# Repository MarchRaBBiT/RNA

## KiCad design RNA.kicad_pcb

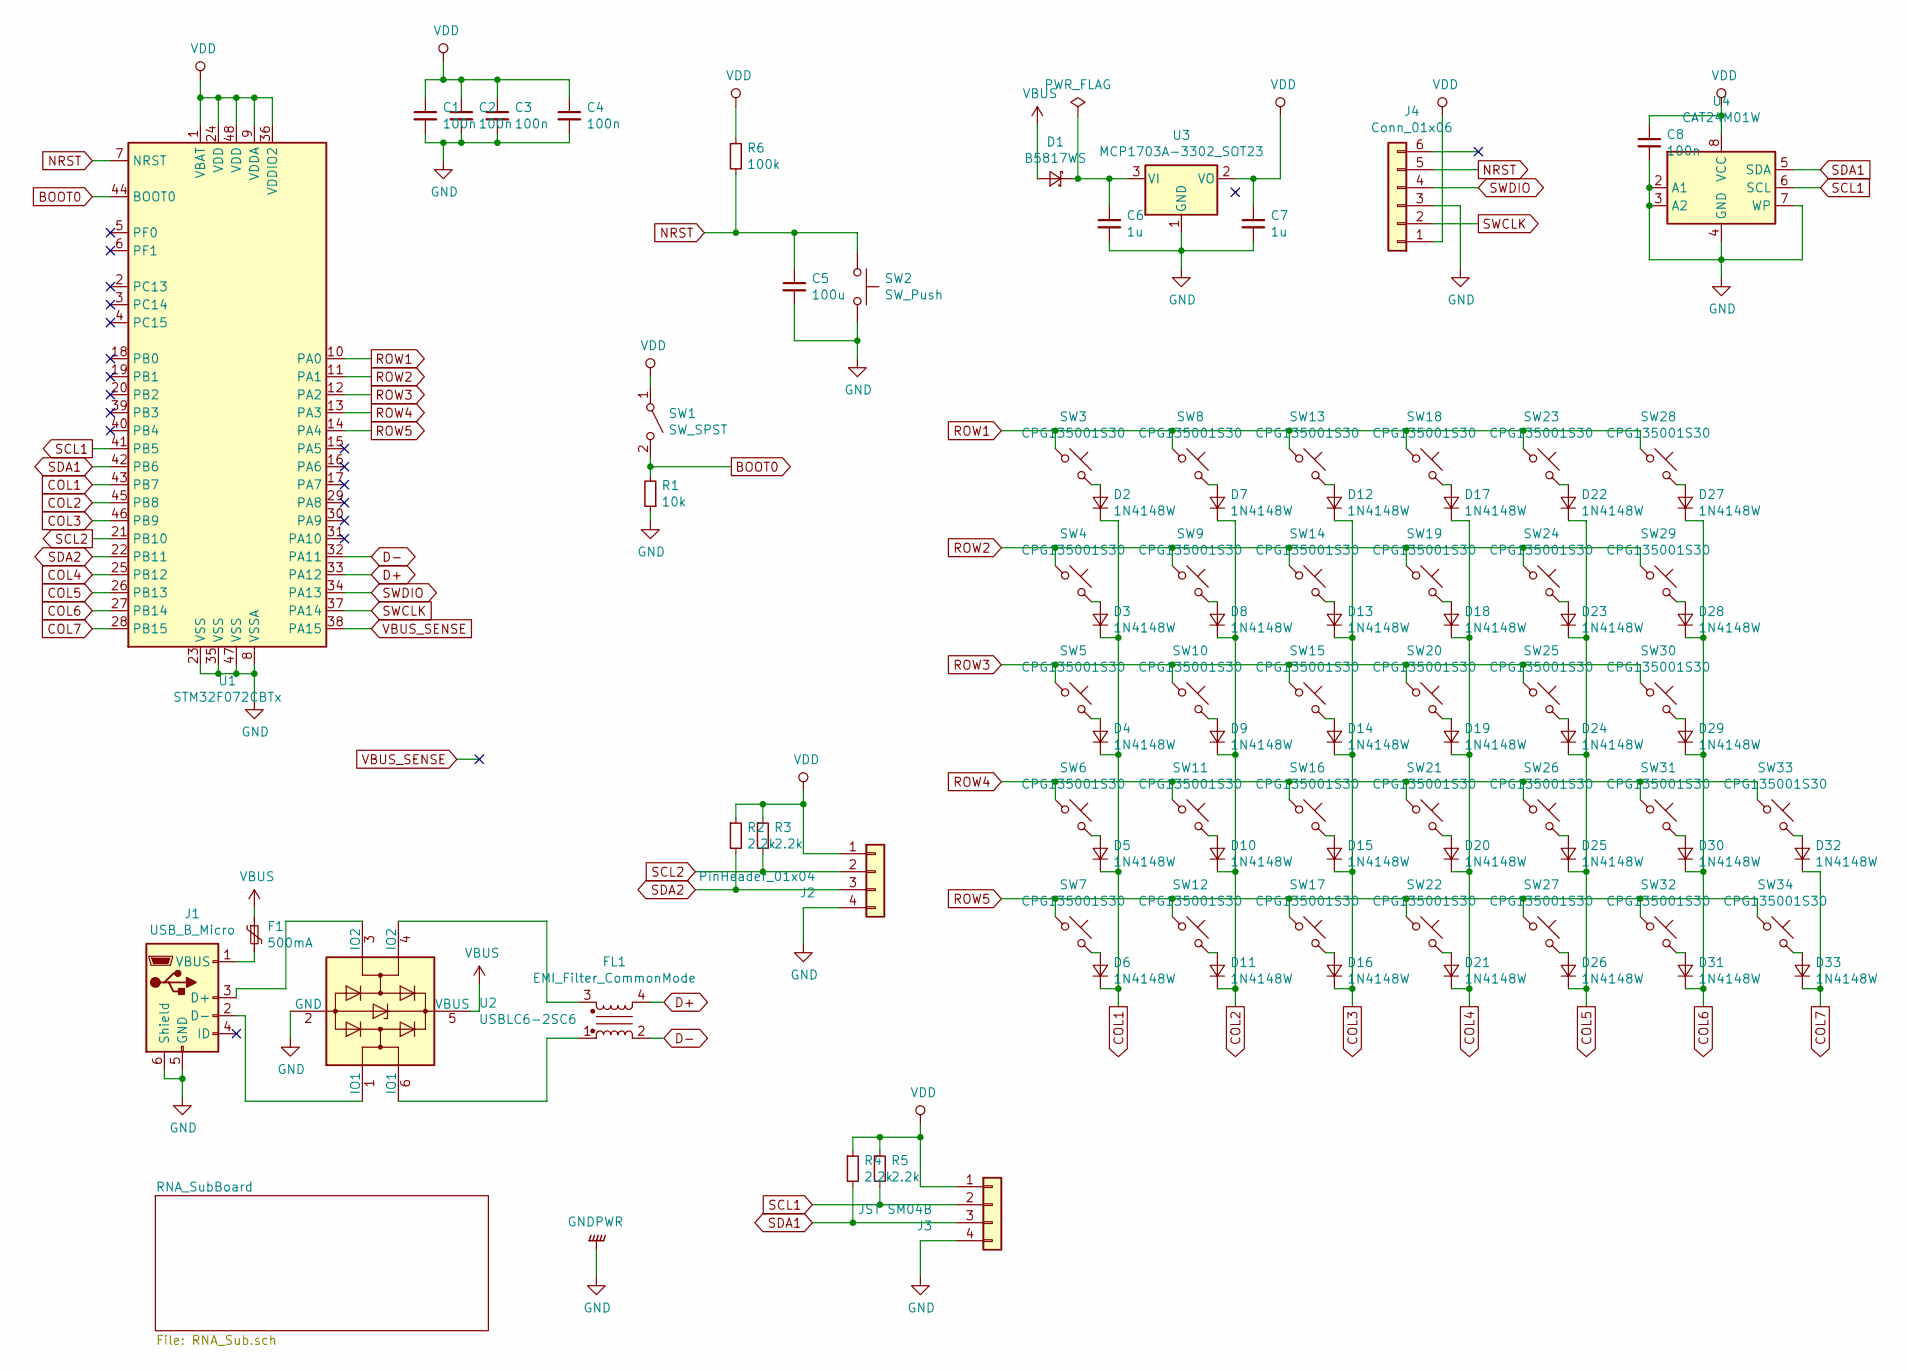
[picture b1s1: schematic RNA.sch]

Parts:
C1, C2, C3, C4, C8: 100n; C_0603_1608Metric; LCSC_Parts_No C14663
C5: 100u; C_0603_1608Metric; LCSC_Parts_No C14663
C6, C7: 1u; C_0603_1608Metric; LCSC_Parts_No C15849
D1: B5817WS; D_SOD-323; LCSC_Parts_No C179720
D2, D3, D4, D5, D6, D7, D8, D9, D10, D11, D12, D13, D14, D15, D16, D17, D18, D19, D20, D21, D22, D23, D24, D25, D26, D27, D28, D29, D30, D31, D32, D33: 1N4148W; D_SOD-123; LCSC_Parts_No C81598
F1: 500mA; Fuse_1206_3216Metric; LCSC_Parts_No C261942
FL1: EMI_Filter_CommonMode; ACM2012-121-2P-T002; LCSC_Parts_No C76571
J1: USB_B_Micro; USB_Micro-B_Molex-105017-0001
J2: PinHeader_01x04; PinHeader_1x04_P2.54mm_Vertical
J3: JST SM04B; JST_SH_SM04B-SRSS-TB_1x04-1MP_P1.00mm_Horizontal
J4: Conn_01x06; PinHeader_2x03_P2.54mm_Vertical
R1: 10k; R_0603_1608Metric; LCSC_Parts_No C25804
R2, R3, R4, R5: 2.2k; R_0603_1608Metric; LCSC_Parts_No C4190
R6: 100k; 0603; LCSC_Parts_No C25803
SW1: SW_SPST; SW_DIP_SPSTx01_Slide_6.7x4.1mm_W8.61mm_P2.54mm_LowProfile
SW2: SW_Push; Panasonic_EVQPUL_EVQPUC
SW3, SW4, SW5, SW6, SW7, SW8, SW9, SW10, SW11, SW12, SW13, SW14, SW15, SW16, SW17, SW18, SW19, SW20, SW21, SW22, SW23, SW24, SW25, SW26, SW27, SW28, SW29, SW30, SW31, SW32, SW33, SW34: CPG135001S30; PG1350_socket
U1: STM32F072CBTx; LQFP-48_7x7mm_P0.5mm; JLCSC_Parts_No C81720
U2: USBLC6-2SC6; SOT-23-6; LCSC_Parts_No C7519
U3: MCP1703A-3302_SOT23; SOT-23; JLCSC_Parts_No C144183
U4: CAT24M01W; SOIC-8_3.9x4.9mm_P1.27mm; LCSC_Parts_No C62273

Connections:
BOOT0: R1.2, SW1.2 (B), U1.44 (BOOT0)
COL1: D2.1 (K), D3.1 (K), D4.1 (K), D5.1 (K), D6.1 (K), U1.43 (PB7)
COL2: D7.1 (K), D8.1 (K), D9.1 (K), D10.1 (K), D11.1 (K), U1.45 (PB8)
COL3: D12.1 (K), D13.1 (K), D14.1 (K), D15.1 (K), D16.1 (K), U1.46 (PB9)
COL4: D17.1 (K), D18.1 (K), D19.1 (K), D20.1 (K), D21.1 (K), U1.25 (PB12)
COL5: D22.1 (K), D23.1 (K), D24.1 (K), D25.1 (K), D26.1 (K), U1.26 (PB13)
COL6: D27.1 (K), D28.1 (K), D29.1 (K), D30.1 (K), D31.1 (K), U1.27 (PB14)
COL7: D32.1 (K), D33.1 (K), U1.28 (PB15)
D+: FL1.4, U1.33 (PA12)
D-: FL1.2, U1.32 (PA11)
GND: C1.2, C2.2, C3.2, C4.2, C5.2, C6.2, C7.2, C8.2, J1.5 (GND), J1.6 (Shield), J2.4, J3.4, J4.3, R1.1, SW2.2, U1.8 (VSSA), U1.23 (VSS), U1.35 (VSS), U1.47 (VSS), U2.2 (GND), U3.1 (GND), U4.2 (A1), U4.3 (A2), U4.4 (GND), U4.7 (WP); also elsewhere on the board
NRST: C5.1, J4.5, R6.2, SW2.1, U1.7 (NRST)
unnamed: C6.1, D1.1 (K), U3.3 (VI)
unnamed: D2.2 (A), SW3.2
unnamed: D3.2 (A), SW4.2
unnamed: D4.2 (A), SW5.2
unnamed: D5.2 (A), SW6.2
unnamed: D6.2 (A), SW7.2
unnamed: D7.2 (A), SW8.2
unnamed: D8.2 (A), SW9.2
unnamed: D9.2 (A), SW10.2
unnamed: D10.2 (A), SW11.2
unnamed: D11.2 (A), SW12.2
unnamed: D12.2 (A), SW13.2
unnamed: D13.2 (A), SW14.2
unnamed: D14.2 (A), SW15.2
unnamed: D15.2 (A), SW16.2
unnamed: D16.2 (A), SW17.2
unnamed: D17.2 (A), SW18.2
unnamed: D18.2 (A), SW19.2
unnamed: D19.2 (A), SW20.2
unnamed: D20.2 (A), SW21.2
unnamed: D21.2 (A), SW22.2
unnamed: D22.2 (A), SW23.2
unnamed: D23.2 (A), SW24.2
unnamed: D24.2 (A), SW25.2
unnamed: D25.2 (A), SW26.2
unnamed: D26.2 (A), SW27.2
unnamed: D27.2 (A), SW28.2
unnamed: D28.2 (A), SW29.2
unnamed: D29.2 (A), SW30.2
unnamed: D30.2 (A), SW31.2
unnamed: D31.2 (A), SW32.2
unnamed: D32.2 (A), SW33.2
unnamed: D33.2 (A), SW34.2
unnamed: F1.2, J1.1 (VBUS)
unnamed: FL1.1, U2.6 (IO1)
unnamed: FL1.3, U2.4 (IO2)
unnamed: J1.2 (D-), U2.1 (IO1)
unnamed: J1.3 (D+), U2.3 (IO2)
ROW1: SW3.1, SW8.1, SW13.1, SW18.1, SW23.1, SW28.1, U1.10 (PA0)
ROW2: SW4.1, SW9.1, SW14.1, SW19.1, SW24.1, SW29.1, U1.11 (PA1)
ROW3: SW5.1, SW10.1, SW15.1, SW20.1, SW25.1, SW30.1, U1.12 (PA2)
ROW4: SW6.1, SW11.1, SW16.1, SW21.1, SW26.1, SW31.1, SW33.1, U1.13 (PA3)
ROW5: SW7.1, SW12.1, SW17.1, SW22.1, SW27.1, SW32.1, SW34.1, U1.14 (PA4)
SCL1: J3.2, R5.2, U1.41 (PB5), U4.6 (SCL)
SCL2: J2.2, R3.2, U1.21 (PB10)
SDA1: J3.3, R4.2, U1.42 (PB6), U4.5 (SDA)
SDA2: J2.3, R2.2, U1.22 (PB11)
SWCLK: J4.2, U1.37 (PA14)
SWDIO: J4.4, U1.34 (PA13)
VBUS: D1.2 (A), F1.1, U2.5 (VBUS)
VBUS_SENSE: U1.38 (PA15)
VDD: C1.1, C2.1, C3.1, C4.1, C7.1, C8.1, J2.1, J3.1, J4.1, R2.1, R3.1, R4.1, R5.1, R6.1, SW1.1 (A), U1.1 (VBAT), U1.9 (VDDA), U1.24 (VDD), U1.36 (VDDIO2), U1.48 (VDD), U3.2 (VO), U4.8 (VCC); also elsewhere on the board

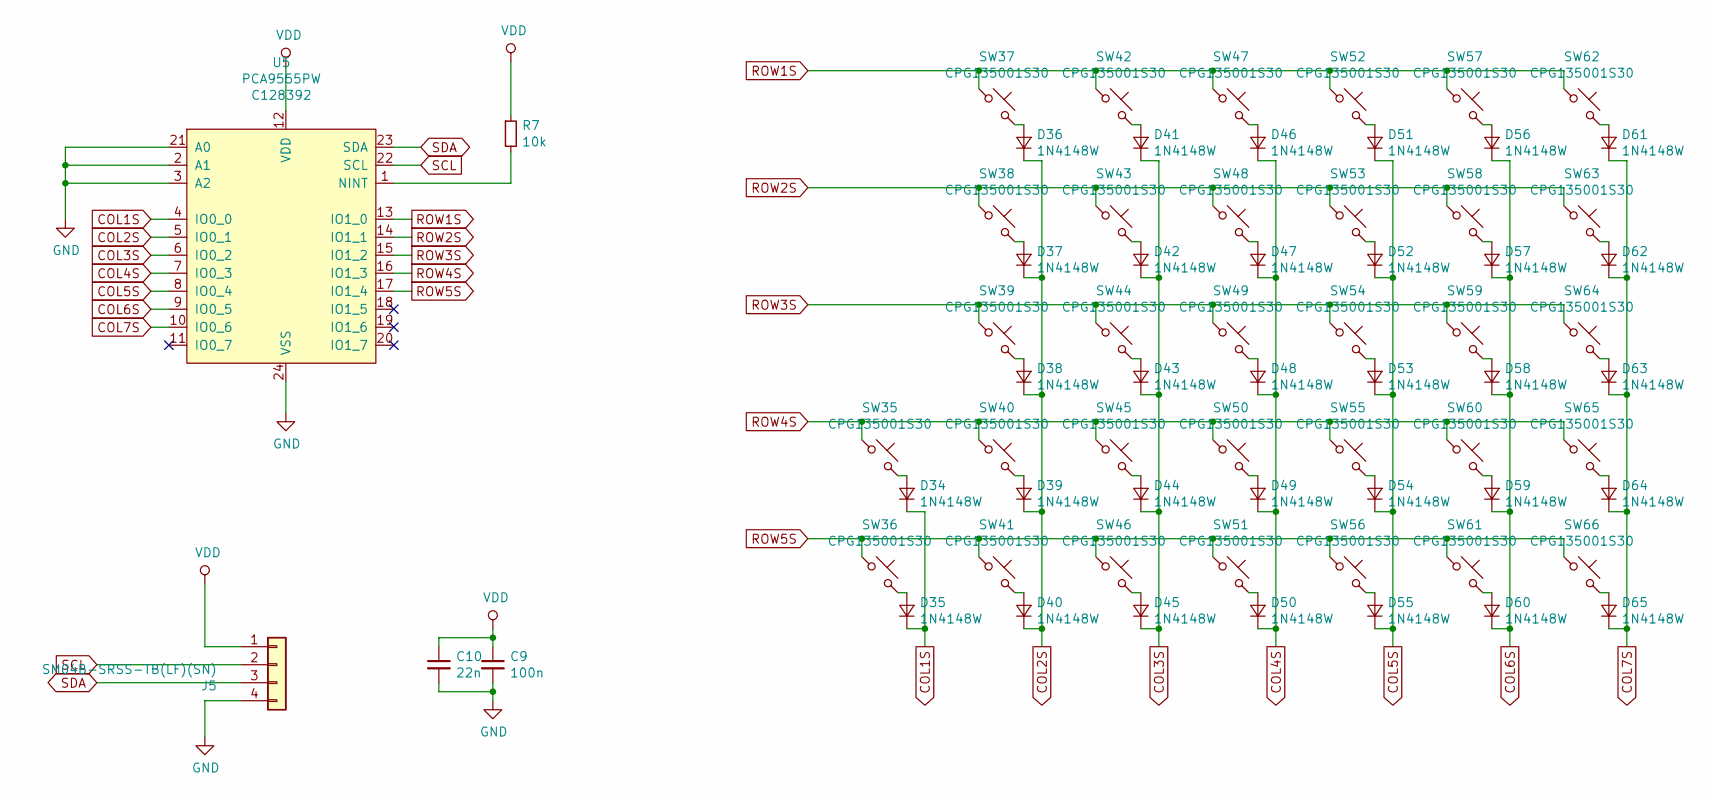
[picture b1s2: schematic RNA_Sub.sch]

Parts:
C9: 100n; C_0603_1608Metric
C10: 22n; C_0603_1608Metric; LCSC_Parts_No C21122
D34, D35, D36, D37, D38, D39, D40, D41, D42, D43, D44, D45, D46, D47, D48, D49, D50, D51, D52, D53, D54, D55, D56, D57, D58, D59, D60, D61, D62, D63, D64, D65: 1N4148W; D_SOD-123; LCSC_Parts_No C81598
J5: SM04B-SRSS-TB(LF)(SN); JST_SH_SM04B-SRSS-TB_1x04-1MP_P1.00mm_Horizontal
R7: 10k; R_0603_1608Metric; LCSC_Parts_No C25804
SW35, SW36, SW37, SW38, SW39, SW40, SW41, SW42, SW43, SW44, SW45, SW46, SW47, SW48, SW49, SW50, SW51, SW52, SW53, SW54, SW55, SW56, SW57, SW58, SW59, SW60, SW61, SW62, SW63, SW64, SW65, SW66: CPG135001S30; PG1350_socket
U5: PCA9555PW; TSSOP-24_4.4x7.8mm_P0.65mm; LCSC_Parts_No C128392

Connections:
COL1S: D34.1 (K), D35.1 (K), U5.4 (IO0_0)
COL2S: D36.1 (K), D37.1 (K), D38.1 (K), D39.1 (K), D40.1 (K), U5.5 (IO0_1)
COL3S: D41.1 (K), D42.1 (K), D43.1 (K), D44.1 (K), D45.1 (K), U5.6 (IO0_2)
COL4S: D46.1 (K), D47.1 (K), D48.1 (K), D49.1 (K), D50.1 (K), U5.7 (IO0_3)
COL5S: D51.1 (K), D52.1 (K), D53.1 (K), D54.1 (K), D55.1 (K), U5.8 (IO0_4)
COL6S: D56.1 (K), D57.1 (K), D58.1 (K), D59.1 (K), D60.1 (K), U5.9 (IO0_5)
COL7S: D61.1 (K), D62.1 (K), D63.1 (K), D64.1 (K), D65.1 (K), U5.10 (IO0_6)
GND: C9.2, C10.2, J5.4, U5.2 (A1), U5.3 (A2), U5.21 (A0), U5.24 (VSS); also elsewhere on the board
unnamed: D34.2 (A), SW35.2
unnamed: D35.2 (A), SW36.2
unnamed: D36.2 (A), SW37.2
unnamed: D37.2 (A), SW38.2
unnamed: D38.2 (A), SW39.2
unnamed: D39.2 (A), SW40.2
unnamed: D40.2 (A), SW41.2
unnamed: D41.2 (A), SW42.2
unnamed: D42.2 (A), SW43.2
unnamed: D43.2 (A), SW44.2
unnamed: D44.2 (A), SW45.2
unnamed: D45.2 (A), SW46.2
unnamed: D46.2 (A), SW47.2
unnamed: D47.2 (A), SW48.2
unnamed: D48.2 (A), SW49.2
unnamed: D49.2 (A), SW50.2
unnamed: D50.2 (A), SW51.2
unnamed: D51.2 (A), SW52.2
unnamed: D52.2 (A), SW53.2
unnamed: D53.2 (A), SW54.2
unnamed: D54.2 (A), SW55.2
unnamed: D55.2 (A), SW56.2
unnamed: D56.2 (A), SW57.2
unnamed: D57.2 (A), SW58.2
unnamed: D58.2 (A), SW59.2
unnamed: D59.2 (A), SW60.2
unnamed: D60.2 (A), SW61.2
unnamed: D61.2 (A), SW62.2
unnamed: D62.2 (A), SW63.2
unnamed: D63.2 (A), SW64.2
unnamed: D64.2 (A), SW65.2
unnamed: D65.2 (A), SW66.2
unnamed: R7.2, U5.1 (NINT)
ROW1S: SW37.1, SW42.1, SW47.1, SW52.1, SW57.1, SW62.1, U5.13 (IO1_0)
ROW2S: SW38.1, SW43.1, SW48.1, SW53.1, SW58.1, SW63.1, U5.14 (IO1_1)
ROW3S: SW39.1, SW44.1, SW49.1, SW54.1, SW59.1, SW64.1, U5.15 (IO1_2)
ROW4S: SW35.1, SW40.1, SW45.1, SW50.1, SW55.1, SW60.1, SW65.1, U5.16 (IO1_3)
ROW5S: SW36.1, SW41.1, SW46.1, SW51.1, SW56.1, SW61.1, SW66.1, U5.17 (IO1_4)
SCL: J5.2, U5.22 (SCL)
SDA: J5.3, U5.23 (SDA)
VDD: C9.1, C10.1, J5.1, R7.1, U5.12 (VDD); also elsewhere on the board

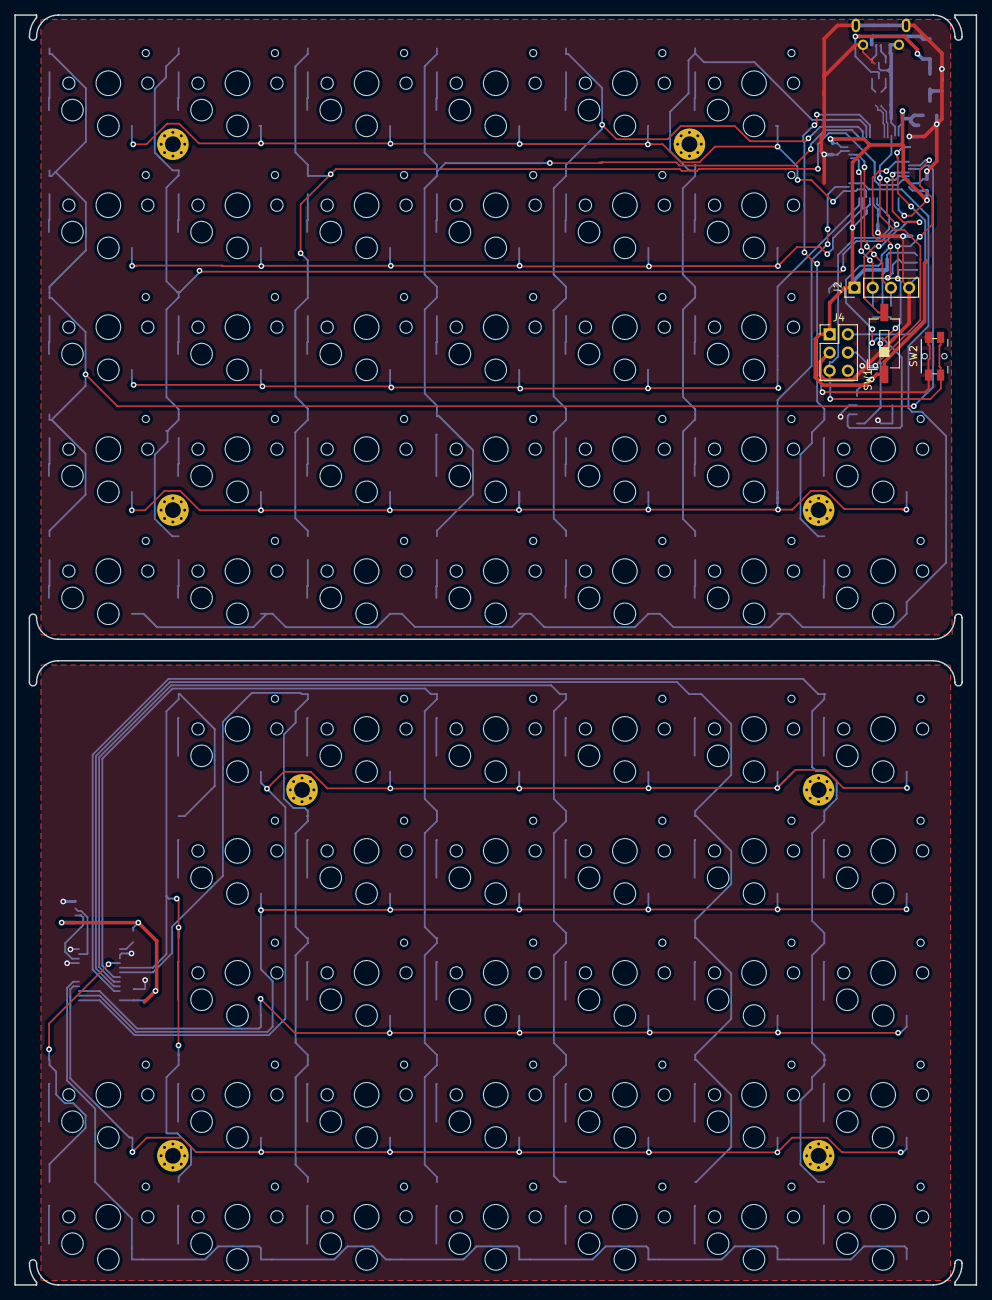
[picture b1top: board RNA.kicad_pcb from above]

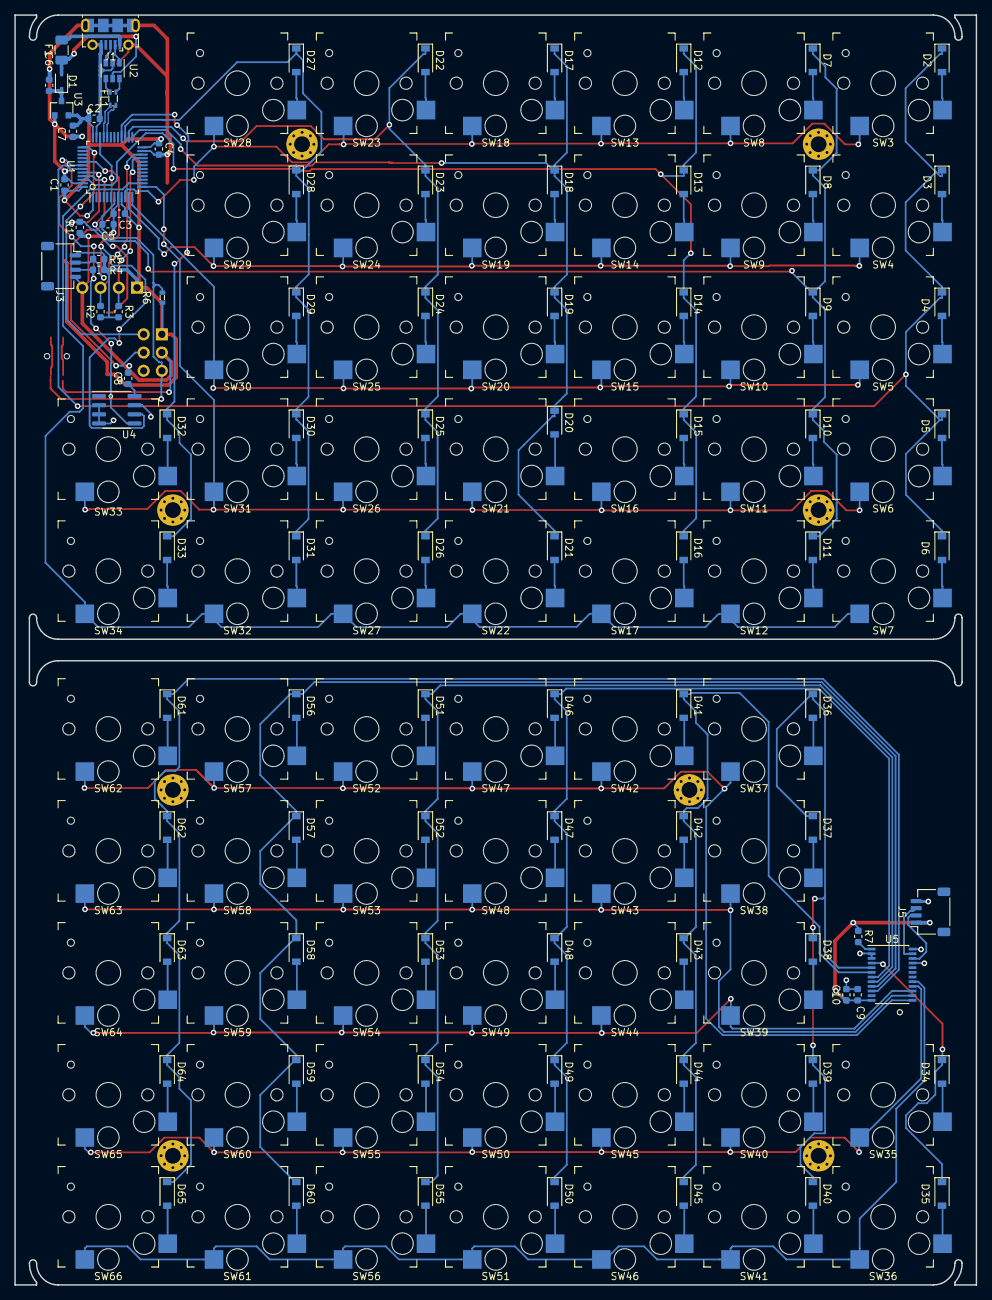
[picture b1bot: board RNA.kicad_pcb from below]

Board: 2 copper layers, 134.0 x 177.0 mm, 160 parts (92 on the bottom side), 110 nets.

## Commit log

2019-01-23 add connectors
2019-01-23 add footprint
2019-01-23 add more footprint
2019-01-24 add more annotation
2019-01-25 add usb reset circuit
2019-01-27 add pcb
2019-06-03 wip"
2019-06-08 fix pcb size
2019-06-09 add sub(right-hand) keyboard
2019-06-09 ready to alpha
2019-06-13 update annotation
2019-06-19 modify module
2019-06-19 arrange reference footprint
2019-06-26 Move conflicted I2C1 to I2C3
2019-06-28 add script
2019-06-28 remove backup files
2019-06-28 change EEPROM interface
2019-08-05 more routing
2019-10-23 chenge microcontroller from STM32L433CCT to STM32F072BCT
2019-11-05 add pull-up resistor for NRST
